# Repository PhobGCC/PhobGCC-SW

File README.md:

# PhobGCC

PhobGCC is an open-source Gamecube controller motherboard aiming to make an accessible and consistent controller. The key feature is the use of hall effect sensors instead of potentiometers, which eliminates a wear item. Additonally, it features notch calibration, digital snapback filtering, button remapping, and various trigger configurations.

If you are interested in making one, join the project Discord to ask questions and get the most up to date information: https://discord.gg/eNJ7xWMvxf

You can find all documentation here: https://github.com/PhobGCC/PhobGCC-doc

Board version 1.2:

Hall effect sensors:

Initial prototypes:

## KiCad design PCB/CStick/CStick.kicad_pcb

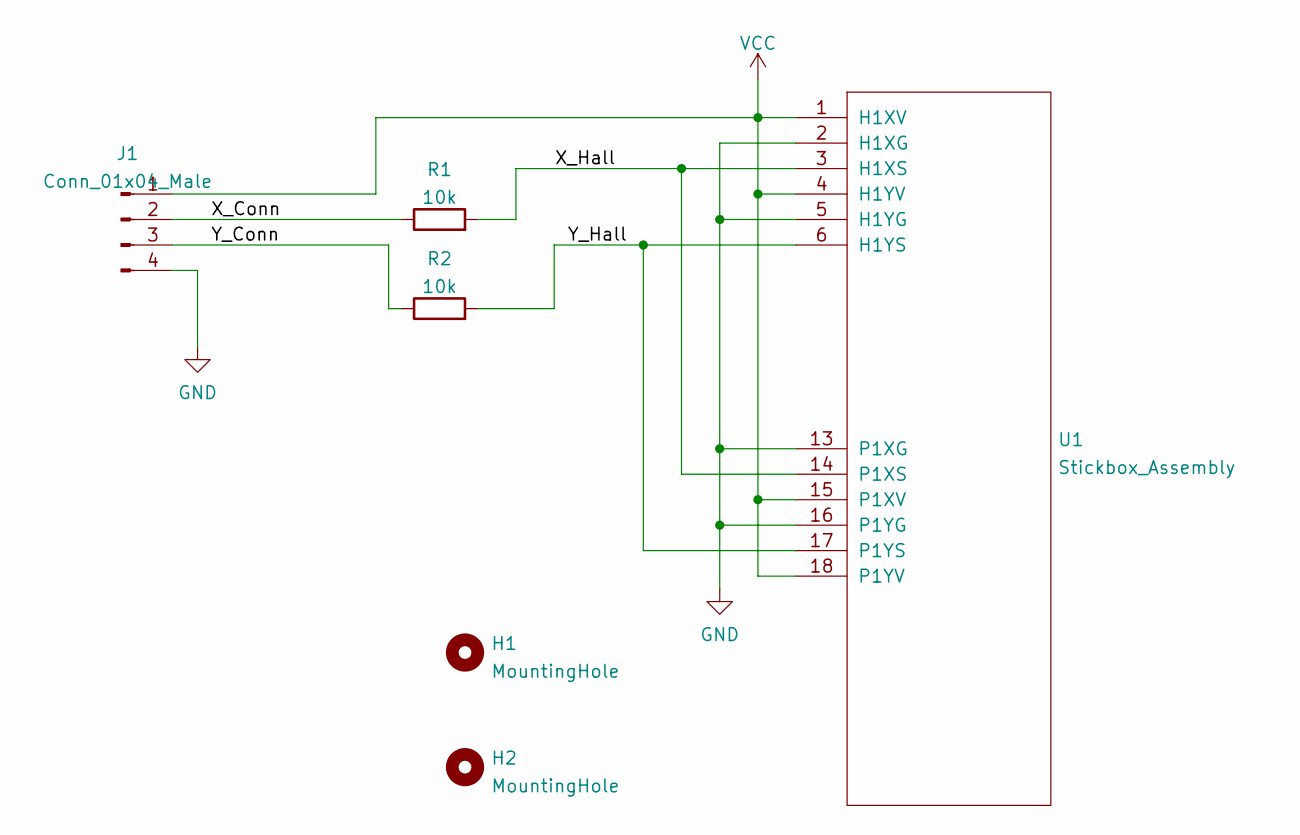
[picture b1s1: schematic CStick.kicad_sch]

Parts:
H1: MountingHole; MountingHole_1.8mm
H2: MountingHole; MountingHole_5.2mm
J1: Conn_01x04_Male; PinHeader_1x04_P2.00mm_Vertical
R1, R2: 10k; R_0603_1608Metric_Pad0.98x0.95mm_HandSolder
U1: Stickbox_Assembly; GCC_Stickbox_2

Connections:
/X_Conn: J1.2, R1.1
/X_Hall: R1.2, U1.3 (H1XS), U1.14 (P1XS)
/Y_Conn: J1.3, R2.1
/Y_Hall: R2.2, U1.6 (H1YS), U1.17 (P1YS)
GND: J1.4, U1.2 (H1XG), U1.5 (H1YG), U1.13 (P1XG), U1.16 (P1YG)
VCC: J1.1, U1.1 (H1XV), U1.4 (H1YV), U1.15 (P1XV), U1.18 (P1YV)

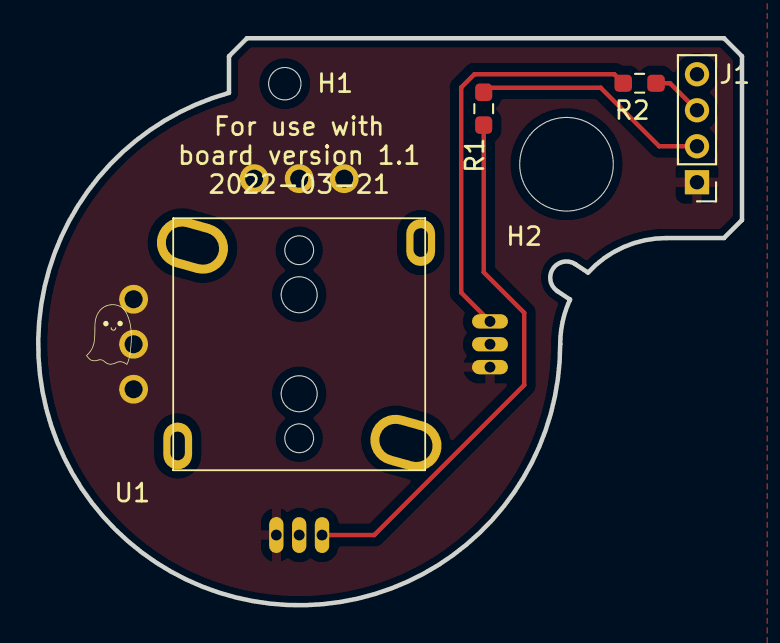
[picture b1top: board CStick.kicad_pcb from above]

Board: 2 copper layers, 39.1 x 31.5 mm, 6 parts (0 on the bottom side), 6 nets.

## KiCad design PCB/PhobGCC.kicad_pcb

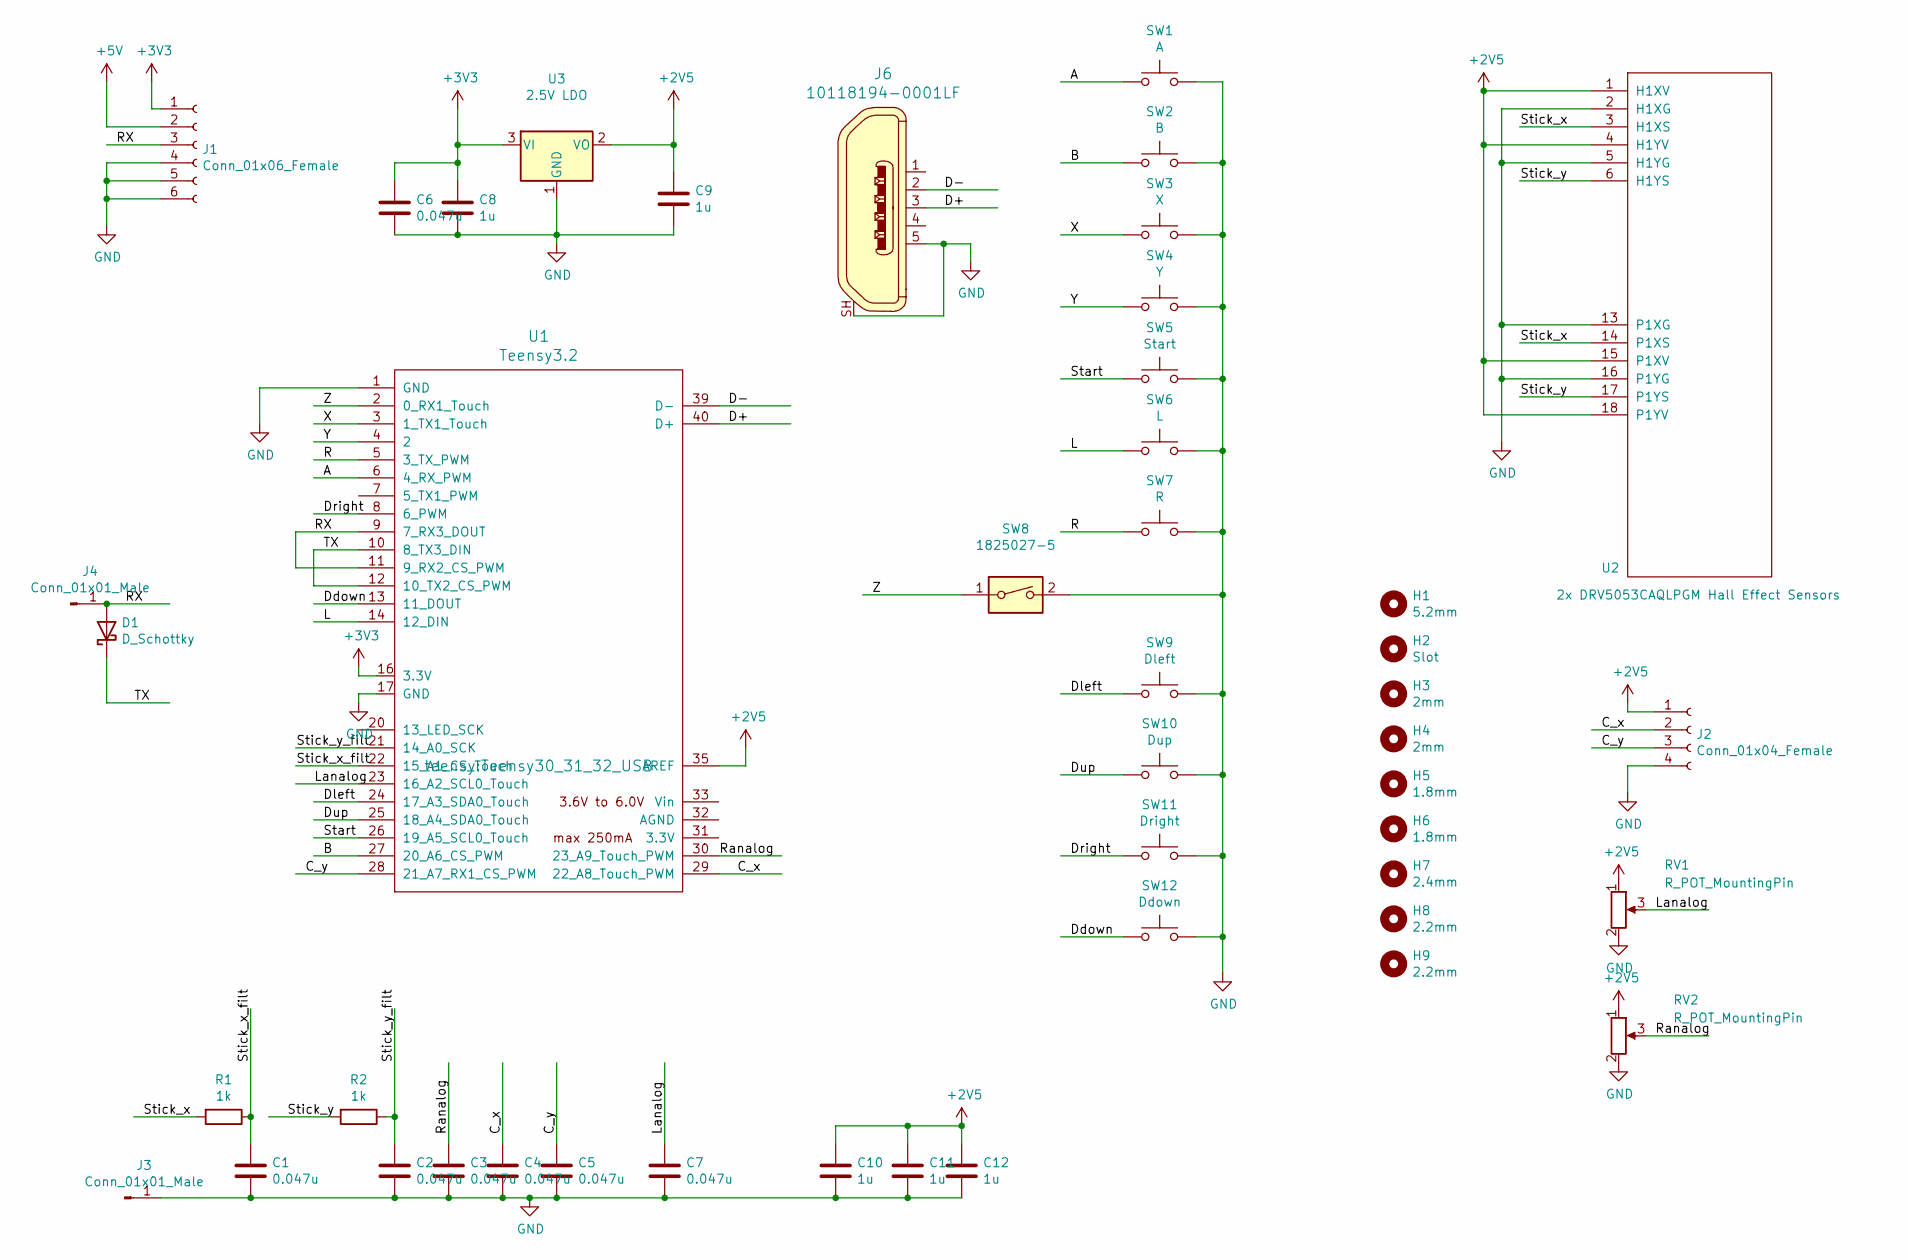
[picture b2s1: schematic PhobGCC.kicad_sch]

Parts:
C1, C2, C3, C4, C5, C6, C7: 0.047u; C_0603_HandSoldering
C8, C9, C10, C11, C12: 1u; C_0603_HandSoldering; MPN CL10A105KB8NNNC; LCSC C15849
D1: D_Schottky; D_SOD-523_large_pads; Manufacturer PN SDM03U40-7; LCSC C151333
H1: 5.2mm; MountingHole_5.2mm
H2: Slot
H3, H4: 2mm; MountingHole_2.0mm
H5, H6: 1.8mm; MountingHole_1.8mm
H7: 2.4mm; MountingHole_2.4mm
H8, H9: 2.2mm; MountingHole_2.2mm
J1: Conn_01x06_Female; GCC_Header_Straight_1x06_Pitch2.00mm
J2: Conn_01x04_Female; Pin_Header_Straight_1x04_Pitch2.00mm
J3, J4: Conn_01x01_Male; PinHeader_1x01_P2.54mm_Vertical
J6: 10118194-0001LF; USB_Micro_B_Female_10118194-0001LF; MPN 10118194-0001LF; Digi-Key_PN 609-4618-1-ND
R1, R2: 1k; R_0603_1608Metric
RV1, RV2: R_POT_MountingPin; GCC_Slider
SW1: A; ABXY_layout_small_mask
SW2: B; ABXY_layout_small_mask
SW3: X; ABXY_layout_small_mask
SW4: Y; ABXY_layout_small_mask
SW5: Start; Start_Contact
SW6: L; Pin_Header_Straight_1x02_Pitch2.54mm
SW7: R; Pin_Header_Straight_1x02_Pitch2.54mm
SW8: 1825027-5; Z_Switch_Edge
SW9: Dleft; Dpad_Contact
SW10: Dup; Dpad_Contact
SW11: Dright; Dpad_Contact
SW12: Ddown; Dpad_Contact
U1: Teensy3.2; Teensy30_31_32_USB
U2: 2x DRV5053CAQLPGM Hall Effect Sensors; GCC_Stickbox_2
U3: 2.5V LDO; SOT-23_Handsoldering; MPN ME6206A25XG; LCSC C236704

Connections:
+2V5: C9.1, C10.1, C11.1, C12.1, J2.1, RV1.1 (V+), RV2.1 (V+), U1.35 (AREF), U2.1 (H1XV), U2.4 (H1YV), U2.15 (P1XV), U2.18 (P1YV), U3.2 (VO)
+3V3: C6.1, C8.1, J1.1, U1.16 (3.3V), U3.3 (VI)
+5V: J1.2
/A: SW1.1, U1.6 (4_RX_PWM)
/B: SW2.1, U1.27 (20_A6_CS_PWM)
/C_x: C4.1, J2.2, U1.29 (22_A8_Touch_PWM)
/C_y: C5.1, J2.3, U1.28 (21_A7_RX1_CS_PWM)
/D+: J6.3, U1.40 (D+)
/D-: J6.2, U1.39 (D-)
/Ddown: SW12.1, U1.13 (11_DOUT)
/Dleft: SW9.1, U1.24 (17_A3_SDA0_Touch)
/Dright: SW11.1, U1.8 (6_PWM)
/Dup: SW10.1, U1.25 (18_A4_SDA0_Touch)
/L: SW6.1, U1.14 (12_DIN)
/Lanalog: C7.1, RV1.3 (Signal), U1.23 (16_A2_SCL0_Touch)
/R: SW7.1, U1.5 (3_TX_PWM)
/RX: D1.2 (A), J1.3, J4.1, U1.9 (7_RX3_DOUT), U1.11 (9_RX2_CS_PWM)
/Ranalog: C3.1, RV2.3 (Signal), U1.30 (23_A9_Touch_PWM)
/Start: SW5.1, U1.26 (19_A5_SCL0_Touch)
/Stick_x: R1.2, U2.3 (H1XS), U2.14 (P1XS)
/Stick_x_filt: C1.1, R1.1, U1.22 (15_A1_CS_Touch)
/Stick_y: R2.2, U2.6 (H1YS), U2.17 (P1YS)
/Stick_y_filt: C2.1, R2.1, U1.21 (14_A0_SCK)
/TX: D1.1 (K), U1.10 (8_TX3_DIN), U1.12 (10_TX2_CS_PWM)
/X: SW3.1, U1.3 (1_TX1_Touch)
/Y: SW4.1, U1.4 (2)
/Z: SW8.1, U1.2 (0_RX1_Touch)
GND: C1.2, C2.2, C3.2, C4.2, C5.2, C6.2, C7.2, C8.2, C9.2, C10.2, C11.2, C12.2, J1.4, J1.5, J1.6, J2.4, J3.1, J6.5, J6.SH, RV1.2 (GND), RV2.2 (GND), SW1.2, SW2.2, SW3.2, SW4.2, SW5.2, SW6.2, SW7.2, SW8.2, SW9.2, SW10.2, SW11.2, SW12.2, U1.1 (GND), U1.17 (GND), U2.2 (H1XG), U2.5 (H1YG), U2.13 (P1XG), U2.16 (P1YG), U3.1 (GND)

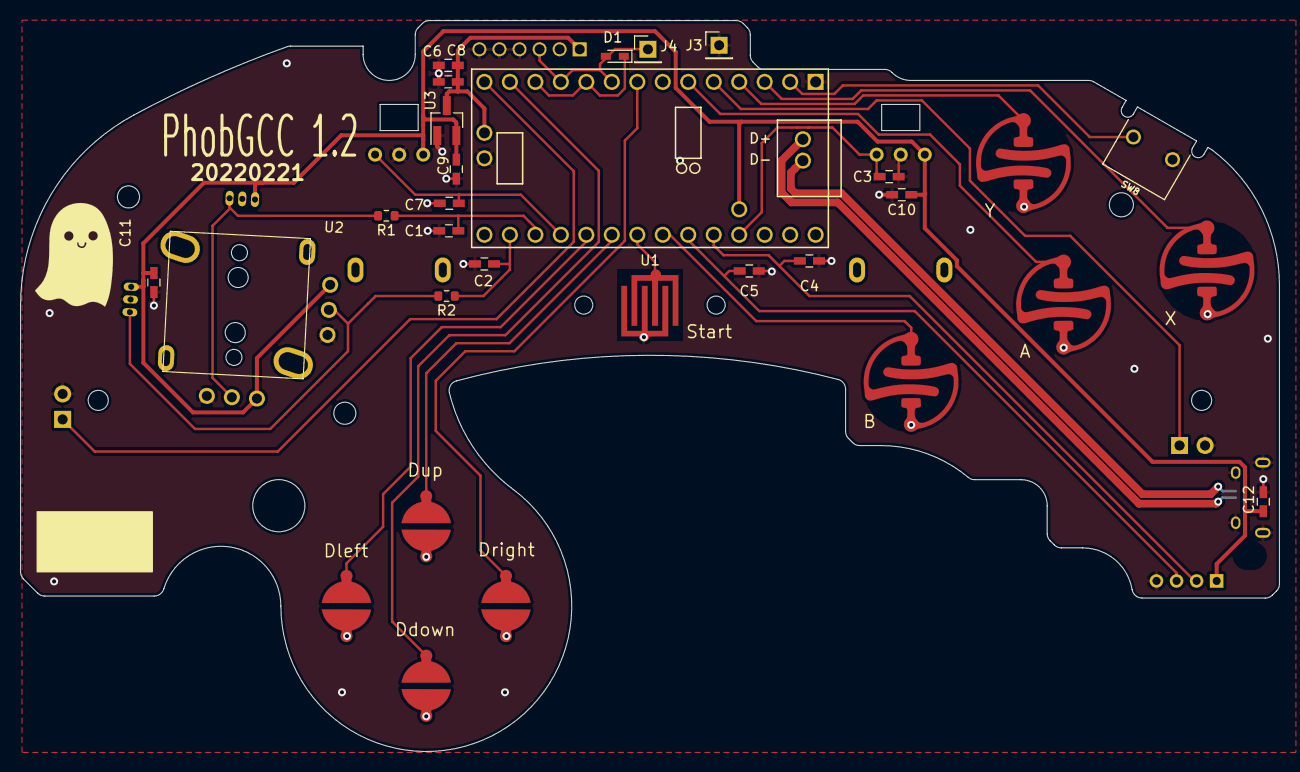
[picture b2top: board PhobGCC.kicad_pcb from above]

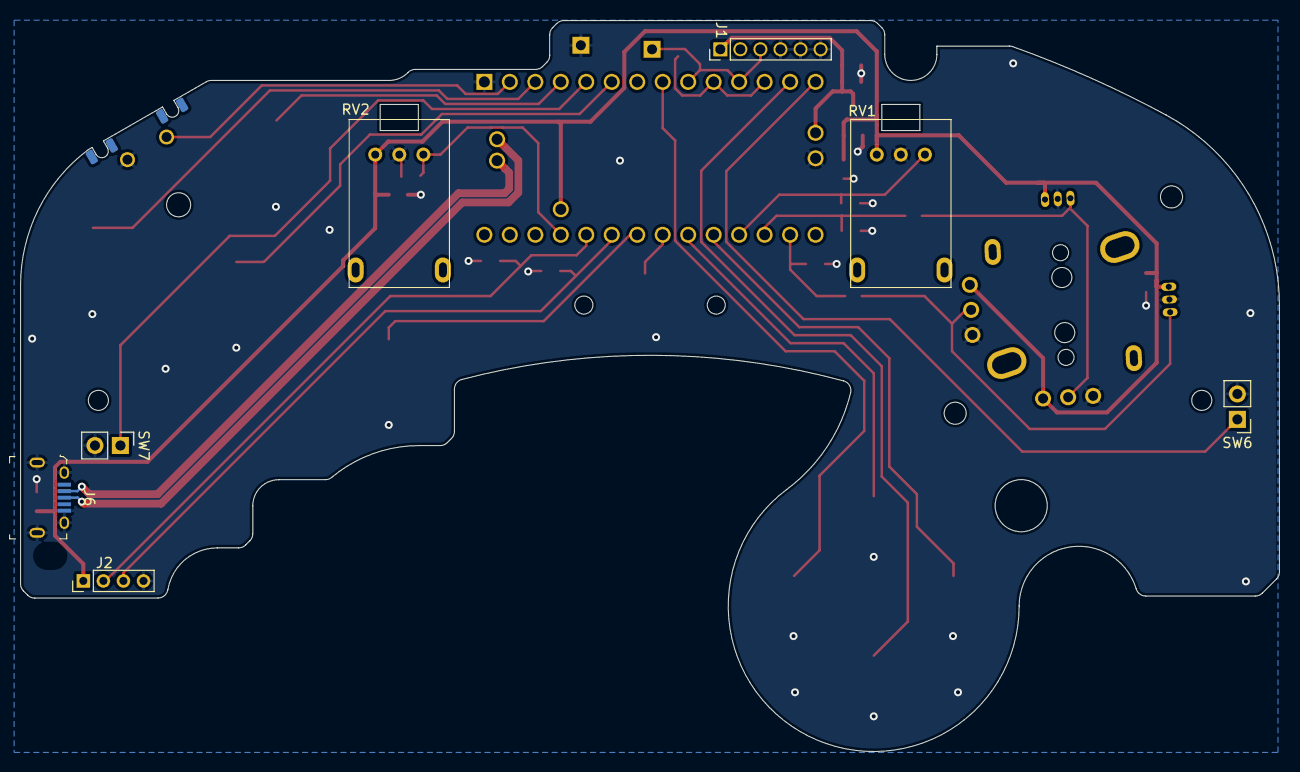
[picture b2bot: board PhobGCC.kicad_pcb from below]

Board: 2 copper layers, 125.5 x 72.9 mm, 46 parts (7 on the bottom side), 27 nets.

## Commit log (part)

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2022-09-21 big overhaul of file structure
2022-09-21 fix dT in readSticks
2022-09-22 add eeprom R toggle to settings.h
2022-09-23 add cstick offset to settings.h
2022-09-25 add snapback and smoothing to settings.h
2022-09-25 move stick cal eeprom to settings.h
2022-09-25 clean up straggler eeprom settings
2022-09-25 clean up currentCalStep global access
2022-09-25 remove _running global access
2022-09-28 fix rumble recall
2022-09-29 remove global tempcalpoints
2022-09-29 remove global notchPoints
2022-09-30 remove advance cal globals
2022-09-30 clean up default cal points
2022-09-30 change spaces to tabs
2022-09-30 add pode filter
2022-10-01 make NotchStatus an enum
2022-10-01 remove global notchStatus arrays
2022-10-01 remove global notchAngles arrays
2022-10-01 remove measuredNotchAngles global
2022-10-01 simplify settings calls for simpler code
2022-10-02 consolidate stick cal param globals
2022-10-02 consolidate repeating applyCalFromStickParams
2022-10-02 major reoganization of settings into phobgcc.h
2022-10-02 comment on bounds for waveshaping control parameter
2022-10-02 reordered waveshaping (still commented)
2022-10-02 move all analog reads into board specific file
2022-10-02 remove last analogread from initializebuttons
2022-10-02 fix teensy 3.2 compilation
2022-10-03 Refactor Extras
2022-10-03 Condense Extras a bit
2022-10-05 Less separation, more integration of Extras
2022-10-05 ifdef extras headers and config printing
2022-10-06 Fix bug preventing setting Extras configs
2022-10-09 typo
2022-10-09 modify example code to use example namespace
2022-10-09 clarify extrasConfigAssign in documentation
2022-10-09 implement new control scheme from Rienne
2022-10-09 enable waveshaping control
2022-10-09 change the waveshaping filter relation
2022-10-09 redo waveshaping setting again
2022-10-10 fix mode 5 triggers
2022-10-11 update nan numbers for waveshaping
2022-10-11 comment out 4.0 line
2022-10-12 make waveshaping work properly
2022-10-12 fix waveshape multiplier calculation
2022-10-15 add factory defaults for streamlining modders' jobs
2022-10-15 Mode 7 Hairtrigger
2022-10-15 Fix cstick notch angle loading
2022-10-15 Move #define enable_led
2022-10-15 implement trigger deadzone of 3
2022-10-15 make collectCalPoints use adcscale on cstick
2022-10-15 Re-writing Mode 7
2022-10-16 BREAK STATEMENTS ARE REQUIRED IN C++
2022-10-16 Revert "Re-writing Mode 7"
    This reverts commit 726fbebd302ce808a3d4bb5e6fe58f054bea95ab.
2022-10-16 make readLa readRa floating point internally
2022-10-16 Make Scales Identical between L and R
2022-10-17 mark for release 0.27
2022-10-18 Don't toggle safe mode if L or R are pressed
2022-10-21 initial rp2040 commit, nothing works eyt
2022-10-21 add more includes and libraries
2022-10-21 link to pico documentation
2022-10-21 it compiles and runs
2022-10-22 make it compile now
2022-10-22 adc readout works woooooo
2022-10-23 implement storage routines
2022-10-23 fix capitalization in rp2040 settings
2022-10-23 fix more settings capitalization
2022-10-23 remove min/max issues
2022-10-23 add noop readADCScale to rp2040
2022-10-24 isolate teensy stuff more
2022-10-28 comms compiles
2022-10-29 implement persistence
2022-10-30 now it works
2022-10-30 remove compilation warning, checked on teensy
2022-10-30 Increasing the 1.0 Cardinal Range and Depth
2022-10-30 fix timestep calculation (why didn't it work)
2022-10-30 implement dac
2022-11-01 stripes! 10 writes per frame
2022-11-02 hello world, phob ghost
2022-11-03 initial drawLine commit
2022-11-05 it works, and reads button inputs
2022-11-06 kinda draws letters? badly
2022-11-07 images and text work, lines don't seem to?
    if there's too much at once it starts flickering or something
2022-11-09 IT WORKS IT WAS SO EASY
2022-11-11 enable grayscale text
2022-11-11 add sync variables
2022-11-12 1khz adc plus video works at the same time!?!?!?!
    why
    I don't get it
    why didn't it work before, why is it working now
2022-11-12 remove sync, don't know why it works still
2022-11-12 make A toggle 1khz
2022-11-13 implement stickmap graphing
2022-11-13 add back in missing dpad pins
2022-11-13 it seems to work but the stick won't calibrate
2022-11-15 fixed the freezing after 2^32 us on teensy
2022-11-16 make comms respond faster, fix teensy filter
2022-11-19 beef up lower case letters verticals to 2px
2022-11-20 tweak t and f crossbars
2022-11-22 Revert "make comms respond faster, fix teensy filter"
    This reverts commit 32ab8e2fa3150d35eb7809aae3261c046a190f3e.
2022-11-24 output the linearized stick angle
2022-11-25 better number output; some menu work
2022-11-25 now the stick works
2022-11-25 all buttons work
2022-11-26 make the lower case a shorter
2022-11-27 change to mcp3202
2022-12-03 make bad stored settings sane
2022-12-04 Make version settings migration.
2022-12-06 adjust rumble values again
2022-12-06 settings overview done
2022-12-06 add stick debug menu item
2022-12-06 Make rumble disabled stay disabled after migration
2022-12-07 make a factory default for rumble
2022-12-07 board 2.0 header finished; split off proto
2022-12-07 add rumble support
2022-12-08 stick debug menu framework
2022-12-09 add startup delay
2022-12-10 now it runs, but storage doesn't write
2022-12-10 mostly works
2022-12-10 rumble works? maybe?
2022-12-11 stick debug output working
2022-12-11 add instructions to stick debug
2022-12-11 fix readme typo
2022-12-11 revise comment
2022-12-15 include settings in menu.cpp
2022-12-15 reorganize menu, start on asnapback page
2022-12-17 first settings page works
2022-12-17 make saving work properly
2022-12-17 settings page for c snapback
2022-12-18 fix lras in configure mode
2022-12-20 simplify time overflow handling
2022-12-20 make it compile properly on teensy
2022-12-20 mark some menus as done
2022-12-20 button remap menu
2022-12-20 rumble menu
2022-12-23 it almost works
2022-12-24 why doesn't it work
2022-12-27 it's better, but not perfect
2022-12-27 well, it works for now
2022-12-28 autoinit menu & 250mhz overclock
2022-12-28 soft reset menu
2022-12-29 reset works
2022-12-30 restructure cal calls into functions
2023-01-04 lock up for 0.28
2023-01-04 comment out headers
2023-01-07 more thorough fix for oem adapter
2023-01-07 fix notch adjust bug
2023-01-08 cal menu done
2023-01-08 implement input viewer
2023-01-09 v0.28 release
2023-01-11 add coordinates to input viewer
2023-01-11 fix alignment of input viewer coords
2023-01-13 phobvision: add rumble test and interlace offset
2023-01-13 Initial Stick Toggles Commit
    Builds in Analog Scaling and Cardinal Snaping Behavior.
    Note: Cardinal Snapping is not yet applied.
2023-01-13 Compilation Fixes
    Fixes typos to ensure compilation for teensy and rp2040
2023-01-14 make fast change rapid instead of jumping
2023-01-14 Making Cardinal Snapping Stick-Independent
2023-01-14 Compilation Fixes
2023-01-14 Fixing Analog Scaling and Overlapping Commands
2023-01-14 Fix Astick commands overlapping with Cstick ones
2023-01-14 using debug.h instead of #ifdef ARDUINO before every print
2023-01-14 moving debug.h into the HW directories
2023-01-14 make it compile for rp2040, some cleanup
2023-01-17 update build instructions
2023-01-21 reaction time test
2023-01-22 change k from handwriting style
2023-01-30 add stickmaps
2023-02-11 let you step through xyscope
2023-02-11 change xyscope initialize button to a
2023-02-21 Adding Rotario Source
2023-02-21 formatting fix
2023-03-06 part of press time done
2023-03-06 Initial decumulate lockout
2023-03-07 moving safeModeLockout into the controls struct
2023-03-07 Calibration decumulator
2023-03-07 make vars static
2023-03-09 initial tournament toggle commit
2023-03-11 fix copypaste error and remove testing thing
2023-03-11 fix bug in xyscope
2023-03-11 shorten safe mode toggle duration
2023-03-11 disable migration for now
2023-03-13 maybe make xyplot work properly?
2023-03-14 add frame durations to button timing
2023-03-14 move press time waiting... text
2023-03-15 add explanation for negative snapback
2023-03-15 cardinal snapping menu done
2023-03-16 implement stick scaling menu
2023-03-16 tweak cardinal snapping, remove coffset
2023-03-17 fix rounding for cardinals
2023-03-17 show on sticks what tournament toggle you are on
2023-03-17 compile fix v1
2023-03-17 Revert "Dev menu"
2023-03-17 some prep work for recording
2023-03-17 cherry pick tournament toggle rewrite
2023-03-17 get tourney toggle mode working
2023-03-18 shorten tourney mode delay to 1s
2023-03-22 add autorepeat to button timing
2023-03-27 tweak Rienne's role
2023-03-27 updated contributors
2023-03-29 clean up unused drawing code
2023-03-30 make it easier to change the origin
2023-04-07 wider bounds for modder notches only
2023-04-09 Don't toggle safe mode if B or Z are pressed
2023-04-12 make xyplot detection based on raw
2023-04-25 timescope working except for triggers
2023-04-25 polish it a little
2023-04-25 snapback and dashback % work
2023-04-25 pivot percent works
2023-04-25 fix tilde squiggle direction
2023-04-26 use rounded label properly on stick dbg
2023-05-01 make tourneytoggle show on c-stick
2023-05-01 move tourney toggle display from cx to cy
2023-05-01 add 1 to tourney toggle display
2023-05-03 reset phobvision recording when backing out
2023-05-03 make defaults follow the struct
2023-05-09 slightly open up the margin for rescuing notches from the deadzone
2023-05-11 extend deadzone rescue to .3375
2023-05-12 fix migration
2023-05-12 version bump to 30 beta
2023-06-03 make calibration LRA input more responsive
2023-06-03 change tournament toggle command
2023-06-03 re-migrate cardinal stick snapping
2023-06-11 usb serial debug
2023-06-11 disable extras again
2023-10-12 Update digital-only trigger mode with proof of concept impl
2023-10-15 Introduce digital threshold as a new trigger state, update references to trigger modes, use modulo instead of if/else for incrementing trigger modes
2023-10-22 Add mode where analog shielding triggers digital shielding instead. My hands hurt, hard pressing L is unpleasant.
2024-02-25 add flake
2024-03-07 increase waveshaping limits to +-24
2024-03-08 rename high to heavy pode
2024-03-08 fix showsticksettings for negative waveshaping
2024-03-08 allow disabling rumble brake
2024-03-12 phobvision can calculate ucf dashback now
2024-03-14 add migration for smoothing
2024-03-16 0.84 soft cardinal avoidance
2024-03-17 fix some phobvision settings text
2024-04-03 change b press check to hw b
2024-04-16 fix second cal first step
2024-04-17 change initialization B to hardware for teensy too
2024-04-23 increase notch adjust to 2x/0.5x
2024-05-01 Support different Readingmodes
2024-05-01 increase waveshaping accel sensitivity
2024-05-02 make phobvision remember menu index
2024-05-04 fix sub-byte order in mode structs
2024-05-17 add mizuyoukanao to contributors
2024-05-31 sorta compiles?
2024-05-31 it works, on phob 2
2024-05-31 fix remap loading
2024-05-31 fix trigger analog lockout
2024-06-03 add teensy, add freezesticks feedback
2024-06-03 add raw stick output toggle
2024-06-14 paddles move
2024-06-21 add scoring
2024-06-21 make the uncalibrated state output raw stick
2024-06-26 make mode 4 ult-compatible
2024-07-09 fix score
2024-09-12 remove mode 5 conflict, mode 4 ult fix
2024-09-12 restrict analog stick scaling per rules
2024-10-16 Brake rumble only when asked to
2024-10-22 show measured notch coords in phobvision
2024-10-26 adjustable ramp time for rumble
2025-04-24 maybe add compatibility for cubstraption?
2025-05-03 widen lower case A in font
2025-05-08 add trigger modes 8 and 9
2025-07-18 Implement showing of trigger settings
    L+R+Z
    Also adjusted the raw output command from a toggle to an on/off with two
    separate commands L+R+Dup/Ddown
2025-11-09 0.31 updates
2025-11-14 fix trigger settings output command
2025-11-22 add cstick snapping
